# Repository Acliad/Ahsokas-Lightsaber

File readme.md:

# Ahsoka Tano's Lightsaber

<div style="clear: both;"></div>

<figure style="float: right; margin-left: 25px; width: 200px;">
  
  <figcaption>First complete build (minus brass contacts)</figcaption>
</figure>

This repo contains documentation and source files for my build of Ahsoka Tano's lightsaber from Star Wars: The Clone Wars.

<div style="clear: both;"></div>

# TODO:
- [ ] Write complete documentation for repository

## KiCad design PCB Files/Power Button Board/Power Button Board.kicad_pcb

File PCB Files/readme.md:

This folder contains all the PCBs involved in the build.

## PCBs
- `Encoder Board`: This board holds the rotary encoder for settings adjustments (or whatever you like)
- `Power Button Board`: This board holds the main power button for turning the saber on and off
- `Power Core Board`: This board is the guts of the lightsaber. It houses the MCU, LED driver circuitry, and the battery charging circuitry

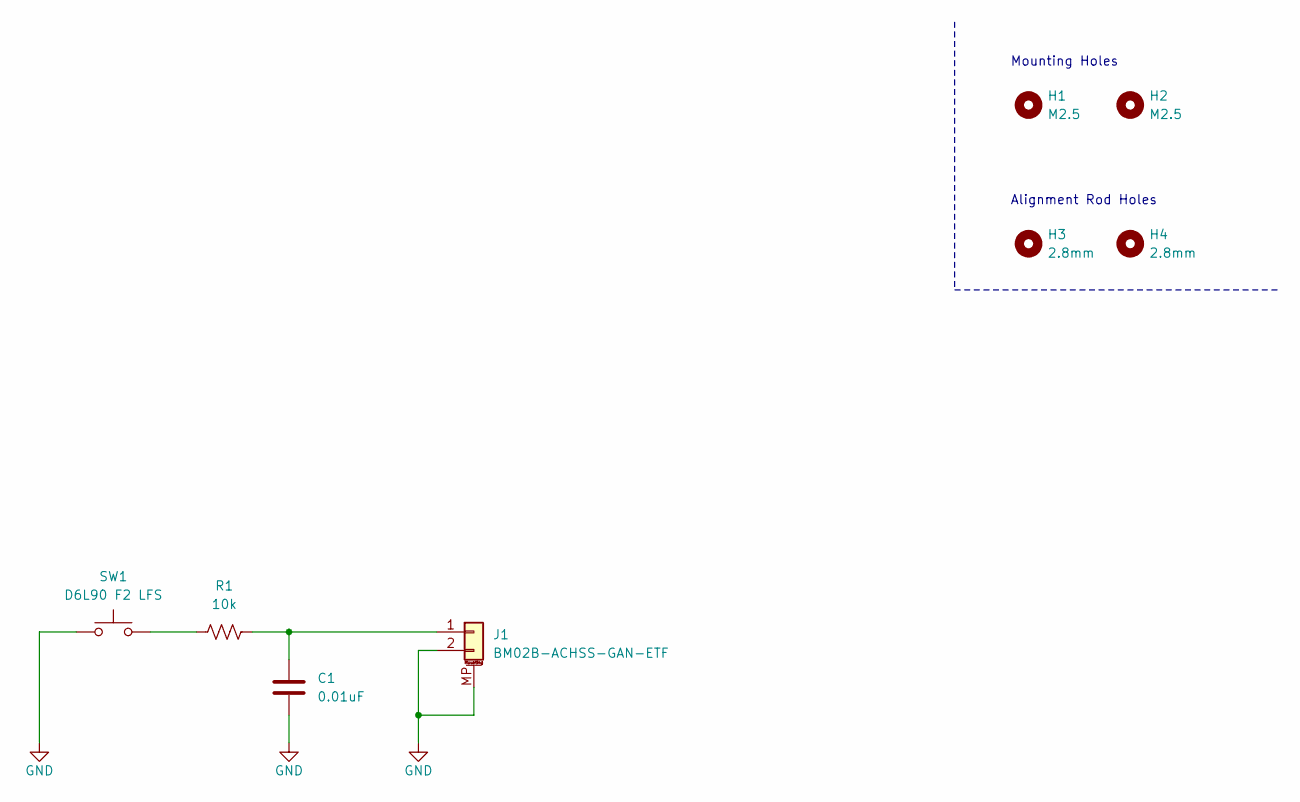
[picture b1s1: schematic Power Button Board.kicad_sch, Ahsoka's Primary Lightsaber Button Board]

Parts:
C1: 0.01uF; C_0603_1608Metric_Pad1.08x0.95mm_HandSolder; DigiKey PN 1276-CL10B103KB8NNNDCT-ND
H1, H2: M2.5; MountingHole_2.7mm_M2.5
H3, H4: 2.8mm; MountingHole_2.8mm_ReducedCourtyard
J1: BM02B-ACHSS-GAN-ETF; JST_ACH_BM02B-ACHSS-GAN-ETF_1x02-1MP_P1.20mm_Vertical; DigiKey PN 455-BM02B-ACHSS-GAN-ETFCT-ND
R1: 10k; R_0603_1608Metric_Pad0.98x0.95mm_HandSolder; DigiKey PN CR0603-FX-1002ELFCT-ND
SW1: D6L90 F2 LFS; SW_CK_D6LxxxxLFS; DigiKey PN 401-2019-ND

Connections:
GND: C1.2, J1.2, J1.MP (MountPin), SW1.1
unnamed: C1.1, J1.1, R1.2
unnamed: R1.1, SW1.2

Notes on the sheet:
Alignment Rod Holes
Mounting Holes

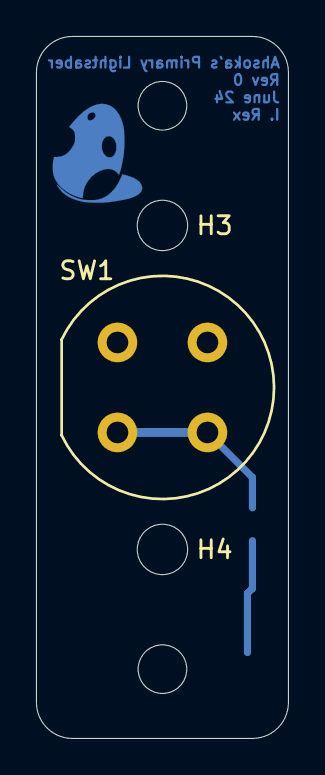
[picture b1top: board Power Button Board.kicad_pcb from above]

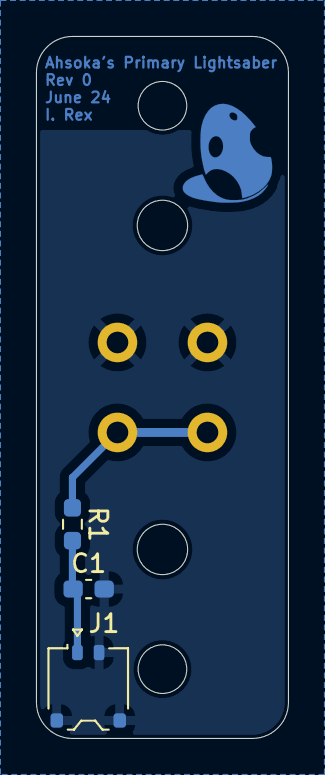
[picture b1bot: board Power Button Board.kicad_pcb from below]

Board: 2 copper layers, 14.0 x 39.0 mm, 8 parts (3 on the bottom side), 3 nets.

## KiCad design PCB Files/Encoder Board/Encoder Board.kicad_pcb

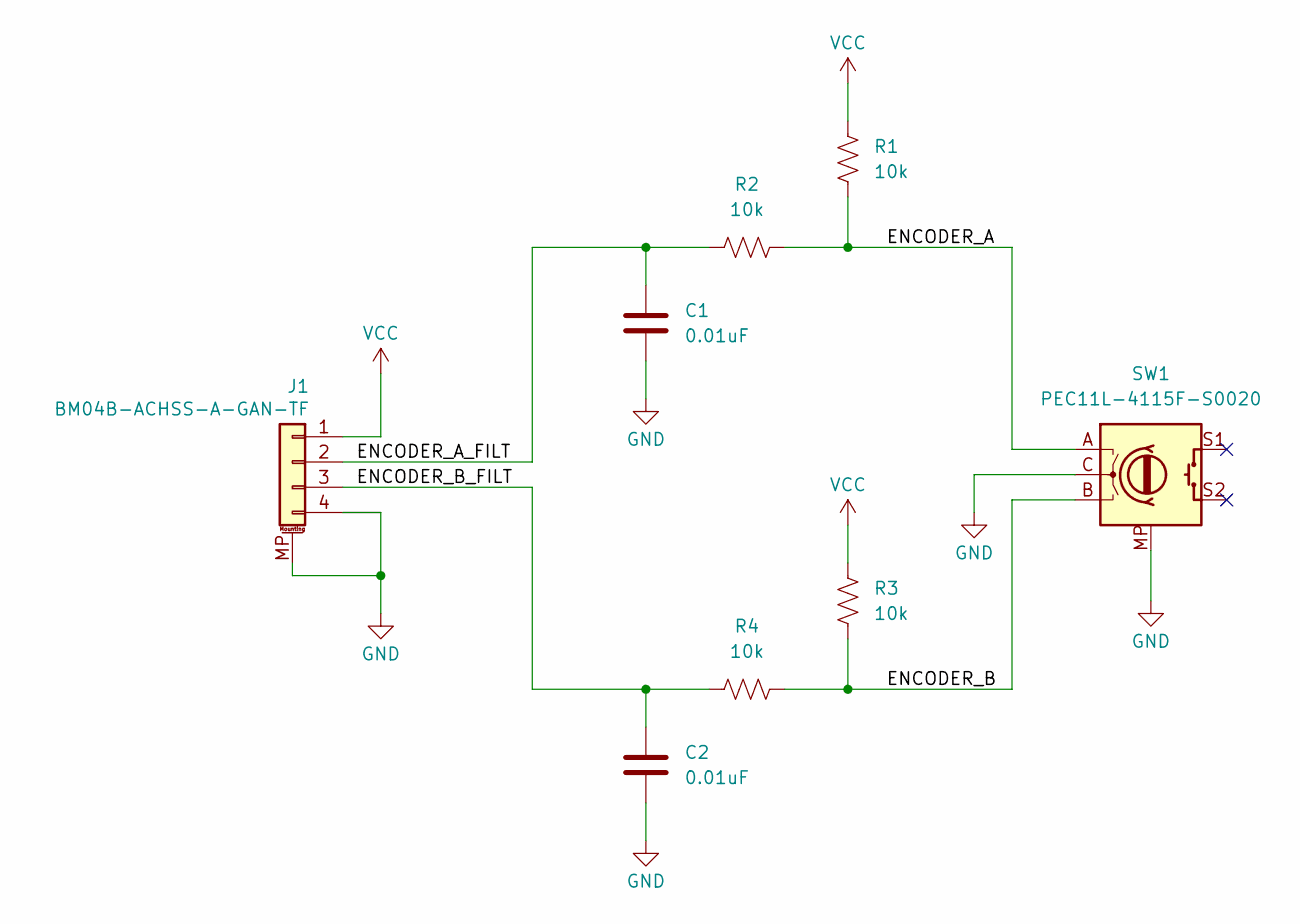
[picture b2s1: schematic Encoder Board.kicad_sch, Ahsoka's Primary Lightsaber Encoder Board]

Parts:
C1, C2: 0.01uF; C_0603_1608Metric_Pad1.08x0.95mm_HandSolder; DigiKey PN 1276-CL10B103KB8NNNDCT-ND
J1: BM04B-ACHSS-A-GAN-TF; JST_ACH_BM04B-ACHSS-A-GAN-ETF_1x04-1MP_P1.20mm_Vertical; DigiKey PN 455-BM04B-ACHSS-A-GAN-TFCT-ND
R1, R2, R3, R4: 10k; R_0603_1608Metric_Pad0.98x0.95mm_HandSolder; DigiKey PN CR0603-FX-1002ELFCT-ND
SW1: PEC11L-4115F-S0020; RotaryEncodoer_Bourns_Vertical_PEC11L-4xxxF-Sxxxx_ShieldPads; DigiKey PN PEC11L-4115F-S0020-ND

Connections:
/ENCODER_A: R1.2, R2.2, SW1.A
/ENCODER_A_FILT: C1.1, J1.2, R2.1
/ENCODER_B: R3.2, R4.2, SW1.B
/ENCODER_B_FILT: C2.1, J1.3, R4.1
GND: C1.2, C2.2, J1.4, J1.MP (MountPin), SW1.C, SW1.MP
VCC: J1.1, R1.1, R3.1

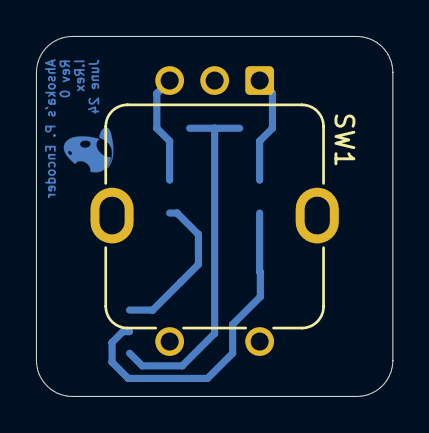
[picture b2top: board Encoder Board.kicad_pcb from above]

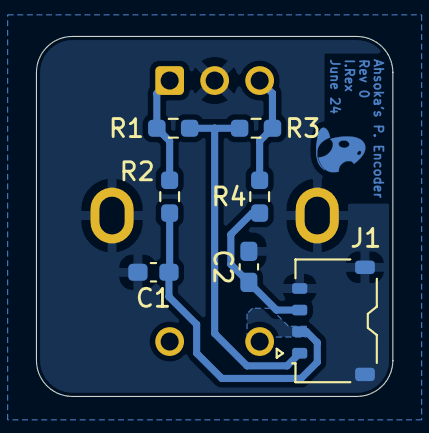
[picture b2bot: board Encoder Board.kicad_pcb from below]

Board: 4 copper layers, 19.8 x 20.0 mm, 8 parts (7 on the bottom side), 6 nets.

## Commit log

2024-09-22 Added some images to main readme
2024-09-22 Updated some HTML in the readme to be github compatible
2024-09-23 Add links to main components in Power Core docs
2024-09-29 Updated gitignore to add some kicad files
2024-09-29 Initial add, power page complete
2024-12-24 Updated to be default off, requires long press
2024-12-24 Fixed no off-mode bug
2025-07-29 Checkpoint before removing VEXT switches
2025-08-01 Schematic drawn, ready for post-wiring
2025-08-03 Added BOM parts, need to make new library part for LED
2025-08-05 Schematic finished, ready for layout
